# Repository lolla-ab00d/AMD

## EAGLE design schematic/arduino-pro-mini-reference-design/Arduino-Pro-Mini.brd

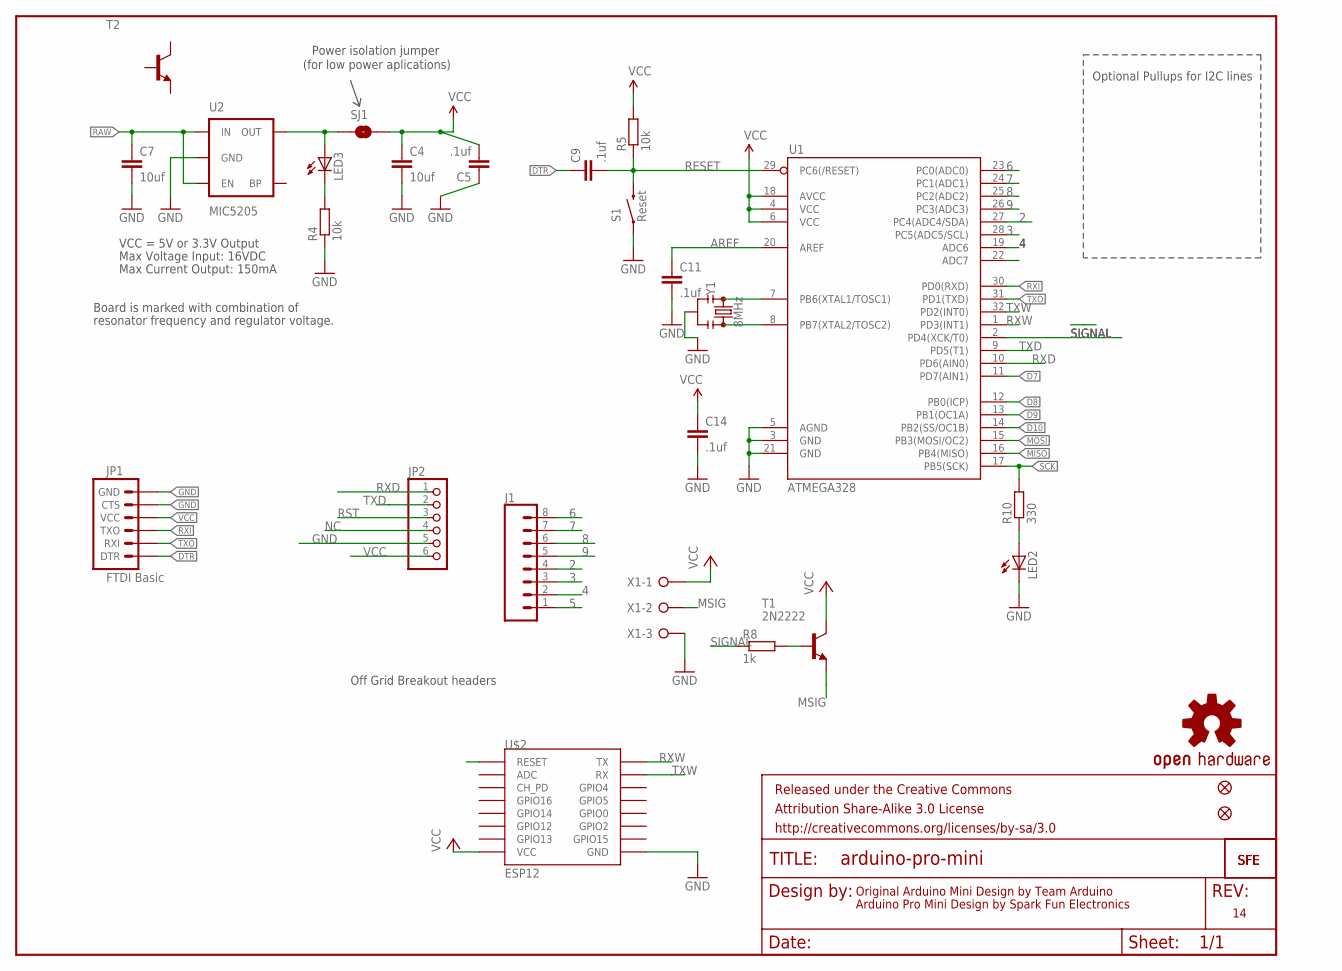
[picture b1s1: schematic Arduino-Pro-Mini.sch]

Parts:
C4, C7: 10uf; C1206
C5, C9, C11, C14: .1uf; C1206
FRAME1: FRAME-LETTER; CREATIVE_COMMONS
J1: CONN_08"; 1X08
JP1: FTDI Basic; 1X06
JP2: PINHD-1X6; 1X06
JP5, JP8: FIDUCIALUFIDUCIAL; MICRO-FIDUCIAL
LED2, LED3: LEDCHIPLED_1206; CHIPLED_1206
R4, R5: 10k; M1206
R8: 1k; M1206
R10: 330; M1206
S1: Reset; TACTILE-SWITCH-SMD-ALT01
SJ1: SOLDERJUMPERNC; SJ_2S
T1: 2N2222; TO92-EBC-OVAL
T2: -NPN-SOT223; SOT223
U1: ATMEGA328; TQFP32-08
U2: MIC5205; SOT23-5
U$1: LOGO-SFESK; SFE-LOGO-FLAME
U$2: ESP12
U$3: OSHW-LOGOS; OSHW-LOGO-S
U$11: LOGO-SFENEW; SFE-NEW-WEBLOGO
X1: W237-3E
Y1: 8MHz; RESONATOR-SMD-3.2X1.3

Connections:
2: J1.4, U1.27 (PC4(ADC4/SDA))
3: J1.3, U1.28 (PC5(ADC5/SCL))
4: J1.2, U1.19 (ADC6)
5: J1.1, U1.22 (ADC7)
6: J1.8, U1.23 (PC0(ADC0))
7: J1.7, U1.24 (PC1(ADC1))
8: J1.6, U1.25 (PC2(ADC2))
9: J1.5, U1.26 (PC3(ADC3))
AREF: C11.1, U1.20 (AREF)
D7: U1.11 (PD7(AIN1))
D8: U1.12 (PB0(ICP))
D9: U1.13 (PB1(OC1A))
D10: U1.14 (PB2(SS/OC1B))
DTR: C9.1, JP1.1 (DTR)
GND: C4.2, C5.1, C7.2, C11.2, C14.2, JP1.5 (CTS), JP1.6 (GND), JP2.5, LED2.C, R4.1, S1.1, S1.2 (1), U1.3 (GND), U1.5 (AGND), U1.21 (GND), U2.2 (GND), U$2.GND, X1.3, Y1.2
MISO: U1.16 (PB4(MISO))
MOSI: U1.15 (PB3(MOSI/OC2))
MSIG: X1.2
unnamed: U1.8 (PB7(XTAL2/TOSC2)), Y1.3
unnamed: U1.7 (PB6(XTAL1/TOSC1)), Y1.1
unnamed: LED3.A, SJ1.1, U2.5 (OUT)
unnamed: LED3.C, R4.2
unnamed: R8.2, T1.B
unnamed: LED2.A, R10.1
NC: JP2.4
RAW: C7.1, U2.1 (IN), U2.3 (EN)
RESET: C9.2, R5.1, S1.3 (2), S1.4 (2), U1.29 (PC6(/RESET))
RST: JP2.3
RXD: JP2.1, U1.10 (PD6(AIN0))
RXI: JP1.3 (TXO), U1.30 (PD0(RXD))
RXW: U1.1 (PD3(INT1)), U$2.TX
SCK: R10.2, U1.17 (PB5(SCK))
SIGNAL: U1.2 (PD4(XCK/T0))
TXD: JP2.2, U1.9 (PD5(T1))
TXO: JP1.2 (RXI), U1.31 (PD1(TXD))
TXW: U1.32 (PD2(INT0)), U$2.RX
VCC: C4.1, C5.2, C14.1, JP1.4 (VCC), JP2.6, R5.2, SJ1.2, T1.C, U1.4 (VCC), U1.6 (VCC), U1.18 (AVCC), U$2.VCC, X1.1

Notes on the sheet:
Original Arduino Mini Design by Team Arduino
Arduino Pro Mini Design by Spark Fun Electronics
Max Voltage Input: 16VDC
Max Current Output: 150mA
Board is marked with combination of
resonator frequency and regulator voltage.
VCC = 5V or 3.3V Output
Optional Pullups for I2C lines
Off Grid Breakout headers
Power isolation jumper
(for low power aplications)

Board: 2 copper layers, 30 parts (0 on the bottom side), 27 nets, no tracks yet.

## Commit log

2017-02-17 ass1
2017-02-21 ass2
2017-03-11 HTML
2017-03-13 schematic
2017-03-18 Nu.of bicycle,rent time,GPS
2017-03-21 presentation2
2017-04-03 proof of concept
2017-04-04 vfinal
2017-04-04 finall1

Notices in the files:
parts and their libraries:
SparkFun-Aesthetics: Licensing: CC v3.0 Share-Alike You are welcome to use this library for commercial purposes.
SparkFun-Aesthetics: Released under the Creative Commons Attribution Share-Alike 3.0 License
SparkFun-Aesthetics: http://creativecommons.org/licenses/by-sa/3.0
